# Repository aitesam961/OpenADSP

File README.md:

> An Embedded solution for Digital Signal Processing Applications in Audio signal processing.

## Table of contents
* [Description](https://github.com/maitesam/OpenADSP/blob/main/README.md#Description)
* [Block Diagram](https://github.com/maitesam/OpenADSP/blob/main/README.md#block-diagram)
* [Working Explained](https://github.com/maitesam/OpenADSP/blob/main/README.md#Working-Explained)
* [Ordering Boards](https://github.com/maitesam/OpenADSP/blob/main/README.md#Ordering-Boards)
* [Assembly](https://github.com/maitesam/OpenADSP/blob/main/README.md#Assembly)
* [Flashing Firmware](https://github.com/maitesam/OpenADSP/blob/main/README.md#Flashing-Firmware)
* [Contribution](https://github.com/maitesam/OpenADSP/blob/main/README.md#Contribution)
* [License](https://github.com/maitesam/OpenADSP/blob/main/README.md#License)

## Description
This device is designed to Take data from Microphone and Process it. Later it could be sent to a wirelessly connected devices Over Bluetooth.
Aside from this, the device can stream data to host computer over USB interface.

The PCB embedds a STM32L432 MCU which is extremely capable of handling Demanding tasks such as Digital Signal Processing.
The DSP scripts could be implemented in the firmware.

## Preview 

## Block Diagram
The Block Diagram Illustrates the connectivity inside The Board.

## Working Explained
This device is Designed for Digital Signal Processing applications.
The idea is to take Audio Data from a microphone, process it & Transmit to client devices.

#### What Type of Processing?
It features an STM32L432 Microcontroller with an ARM Cortex M4F (aka Black Pill). The device can be programmed to Apply Digital Filters and Effects on the audio data.
The very basic example is a Low Pass & High Pass filters.
The Incoming Audio Signal is converted to Digital (By ADC) and then Passed to STM32 which Applies programmed filters.

### Connectivity
The device is loaded with Two modes of communication.

* Bluetooth (2.4GHz)
* USB 2.0

The device is capable of Reading Data, applying filters and then Sending it wirelessly over to a Bluetooth Client
OR 
It Can be used as a USB OTG host device to send data stream over USB 2.0 Interface.

## Ordering Boards
You Can manufacture the PCBs from PCBWay.
[Check Out PCBWay](https://www.pcbway.com/setinvite.aspx?inviteid=440401)

Note: I am not affiliated with PCBWay. However, I just like their service and build quality.

## Assembly Guide
Please Refer to [Hardware Readme](https://github.com/maitesam/OpenADSP/blob/main/Hardware) for Assembly Instructions.

## Flashing Firmware
Please Refer to [Firmware Readme](https://github.com/maitesam/OpenADSP/tree/main/Firmware) to find more details about Flashing FIrmware.

### Contributions

Contributions are what make the open source community such an amazing place to learn, inspire, and create. Any contributions you make are **greatly appreciated**.

If you have a suggestion that would make this better, please fork the repo and create a pull request. You can also simply open an issue with the tag "enhancement".
Don't forget to give the project a star! Thanks again!

1. Fork the Project
2. Create your Feature Branch (`git checkout -b feature/AmazingFeature`)
3. Commit your Changes (`git commit -m 'Add some AmazingFeature'`)
4. Push to the Branch (`git push origin feature/AmazingFeature`)
5. Open a Pull Request

## Roadmap

* [x] Concept Proof
* [x] Research & Information
* [x] Finalizing The Idea
* [x] Schematics
* [x] PCB Design
* [ ] Firmware Development
* [ ] Validation & Testing
* [ ] Documentation
* [ ] Future Improvements

## File Tree

```
.
├── Datasheets
│   ├── AP2112-3.3V.pdf
│   ├── nRF24L01.pdf
│   ├── Readme.md
│   ├── SRV05-4-D.PDF
│   ├── stm32l432kb.pdf
│   └── tlv320aic3100 codec.pdf
├── Documents
│   ├── Code_Print.pdf
│   ├── ibom.html
│   ├── OpenADSP_BLD.jpg
│   ├── OpenADSP_BLD.png
│   ├── PCB Layers
│   │   ├── Audio_Processing_HW_V1.0-B_Adhesive.svg
│   │   ├── Audio_Processing_HW_V1.0-B_Cu.svg
│   │   ├── Audio_Processing_HW_V1.0-B_Mask.svg
│   │   ├── Audio_Processing_HW_V1.0-B_Paste.svg
│   │   ├── Audio_Processing_HW_V1.0-B_Silkscreen.svg
│   │   ├── Audio_Processing_HW_V1.0-Edge_Cuts.svg
│   │   ├── Audio_Processing_HW_V1.0-F_Adhesive.svg
│   │   ├── Audio_Processing_HW_V1.0-F_Cu.svg
│   │   ├── Audio_Processing_HW_V1.0-F_Mask.svg
│   │   ├── Audio_Processing_HW_V1.0-F_Paste.svg
│   │   └── Audio_Processing_HW_V1.0-F_Silkscreen.svg
│   ├── PCB_LayerWise_Export.pdf
│   └── Schematic_OpenADSP.pdf
├── Firmware
│   ├── OpenADSP Debug.launch
│   ├── OpenADSP.ioc
│   ├── Readme.md
│   ├── STM32L432KBUX_FLASH.ld
│   └── temp.html
├── Hardware
│   ├── Analog Filters.kicad_sch
│   ├── Audio_Processing_HW_V1.0.kicad_pcb
│   ├── Audio_Processing_HW_V1.0.kicad_pro
│   ├── Audio_Processing_HW_V1.0.kicad_sch
│   ├── MCU.kicad_sch
│   ├── Power & USB.kicad_sch
│   ├── Readme.md
│   ├── STM32 MCU.kicad_sch
│   ├── untitled.kicad_sch
│   ├── USB&POWER.kicad_sch
│   └── Wireless Tranceiver.kicad_sch
├── Images
│   ├── Bottom_Flat.png
│   ├── Side_Front_view.jpg
│   └── Top_Flat.png
├── LICENSE
├── Mechanical_Files
│   ├── Audio_Processing_HW_V1.0.step
│   ├── Audio_Processing_HW_V1.0.wrl
│   └── readme.txt
├── Readme Docs
│   ├── banner.png
│   ├── ezgif.com-gif-maker.gif
│   ├── icon-5974829_1280.png
│   ├── OpenADSP BOM and 6 more pages - Personal - Microsoft​ Edge 2022-03-02 17-06-42_Trim.mp4
│   ├── OpenADSP.jpg
│   ├── OpenADSP.png
│   └── sound-1837425_1280.png
├── README.md
└── Reference Files
    ├── an4157-stm32f3discovery-peripheral-firmware-examples-stmicroelectronics.pdf
    ├── Deleteme.html
    ├── en.MB1035-F303C-C01_Schematic.pdf
    ├── en.MB1035-F303C-D01_Schematic.pdf
    └── en.MB1035-F303C-E02_Schematic.pdf

9 directories, 59 files

```
## License

This Project is published under General Public License V3.0 See `LICENSE.txt` for more information.
> https://www.gnu.org/licenses/quick-guide-gplv3.html

<p align="right">(<a href="#top">back to top</a>)</p>

* [Jump To Start](https://github.com/maitesam/OpenADSP/blob/main/README.md#Description)

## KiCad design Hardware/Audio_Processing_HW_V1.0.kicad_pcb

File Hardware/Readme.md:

# Readme
## Getting started with Hardware
### Assembly Instructions
Before you start, Get the proper set of equipment.

* The Third Hand is always helpful in assembly. I recommend using some soldering Jig or Stickvise Jaws 
* Its super handy to have a cutting knife
* Better have some Non Serrated Pliers
* Obviously, A soldering Iron
* Solder Paste would be useful
* Great to have some extra Soldering Iron tips to get the perfect size

The Soldering Kit below May give you a good idea of what you need.

## General tips

 * Keep both the schematics and the board file open while you build, you'll likely want to refer back to them more often than not.
 Even I got you covered here. This [Interactive BOM](https://github.com/maitesam/OpenADSP/blob/main/Documents/ibom.html) will help you out locating the components and their references.
 Just Download the file and Open it in your Browser.
 It should present you with something like this

 * I wholeheartedly recommend this thread by [@thingskatedid](https://twitter.com/thingskatedid): https://twitter.com/thingskatedid/status/1348234262886039558

 * **The passives are indistinguishable once taken out of their tapes!**
   * Always work with a single value at a time
   * Only remove as many components from the tape as you need right now
   * Immediately put the tape back into the pouch it came in, as that's where the value is noted - or write the value onto the tape.

 * For each group of passives below, it saves time to batch up different types of operations: First put a small solder blob on one pad of each site, then tack down each component, then solder the other side for all components in a row.

 * If the solder joints on nearby passives blob together a lot, use some flux and a little less solder. It's also a good idea to make a final flux pass across the finished passives just like you would be drag soldering a leaded part, it makes the solder joints look a lot nicer.

### Assembly instructions

These instructions are optimized for hand assembly; the components are grouped in a way that if you follow the groups in order you should never have one component in the way of soldering another. Within a given group the order does not matter; I recommend doing all components of one value before moving on to the next value.

I found this Tutorial Video by @Electronoobs really helpful.

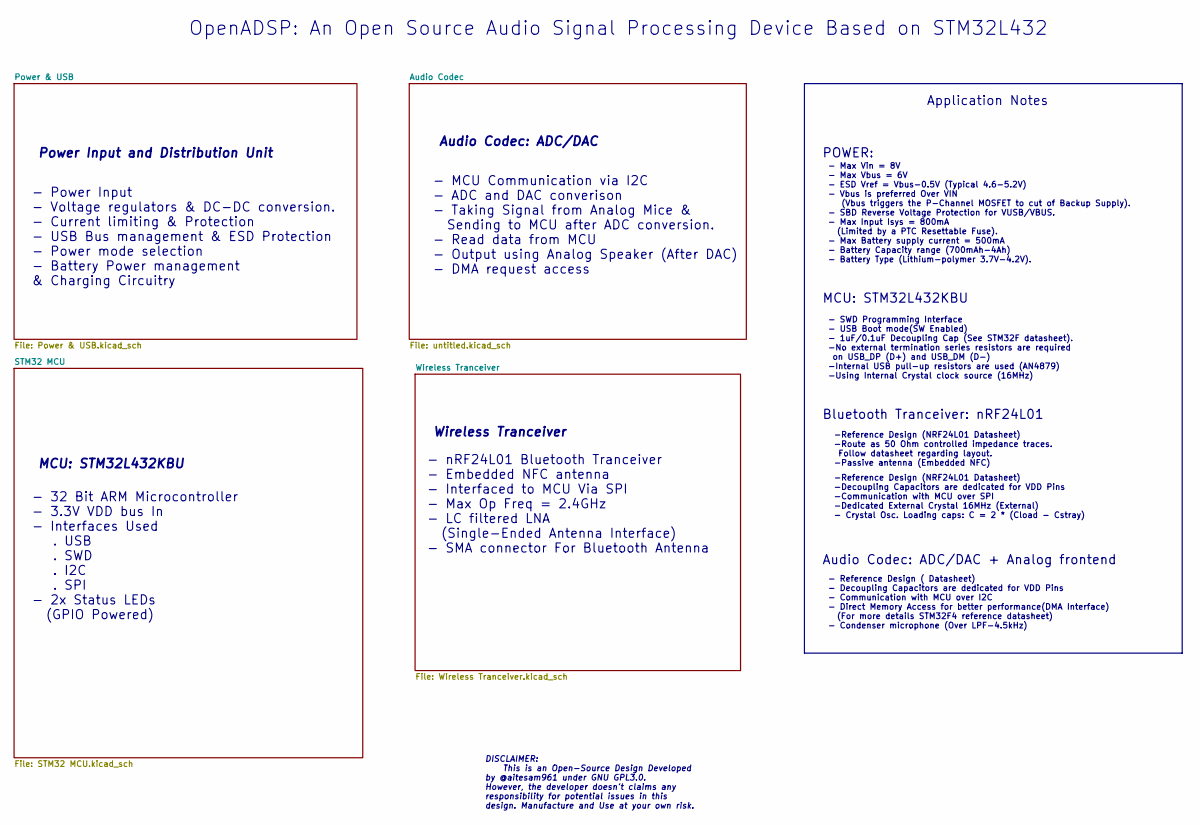
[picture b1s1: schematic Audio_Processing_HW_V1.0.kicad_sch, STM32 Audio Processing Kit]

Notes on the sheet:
OpenADSP: An Open Source Audio Signal Processing Device Based on STM32L432
Audio Codec: ADC/DAC
MCU: STM32L432KBU
- MCU Communication via I2C - ADC and DAC converison - Taking Signal from Analog Mice & Sending to MCU after ADC conversion. - Read data from MCU - Output using Analog Speaker (After DAC) - DMA request access
- nRF24L01 Bluetooth Tranceiver - Embedded NFC antenna - Interfaced to MCU Via SPI - Max Op Freq = 2.4GHz - LC filtered LNA (Single-Ended Antenna Interface) - SMA connector For Bluetooth Antenna
MCU: STM32L432KBU
POWER:
- Reference Design ( Datasheet) - Decoupling Capacitors are dedicated for VDD Pins - Communication with MCU over I2C - Direct Memory Access for better performance(DMA Interface) (For more details STM32F4 reference datasheet) - Condenser microphone (Over LPF-4.5kHz)
- Power Input - Voltage regulators & DC-DC conversion. - Current limiting & Protection - USB Bus management & ESD Protection - Power mode selection - Battery Power management & Charging Circuitry
-Reference Design (NRF24L01 Datasheet) -Decoupling Capacitors are dedicated for VDD Pins -Communication with MCU over SPI -Dedicated External Crystal 16MHz (External) - Crystal Osc. Loading caps: C = 2 * (Cload - Cstray)
Power Input and Distribution Unit
- 32 Bit ARM Microcontroller - 3.3V VDD bus In - Interfaces Used . USB . SWD . I2C . SPI - 2x Status LEDs (GPIO Powered)
Application Notes
- Max Vin = 8V - Max Vbus = 6V - ESD Vref = Vbus-0.5V (Typical 4.6-5.2V) - Vbus is preferred Over VIN (Vbus triggers the P-Channel MOSFET to cut of Backup Supply). - SBD Reverse Voltage Protection for VUSB/VBUS. - Max Input Isys = 800mA (Limited by a PTC Resettable Fuse). - Max Battery supply curre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
Audio Codec: ADC/DAC + Analog frontend
-Reference Design (NRF24L01 Datasheet) -Route as 50 Ohm controlled impedance traces. Follow datasheet regarding layout. -Passive antenna (Embedded NFC)
Bluetooth Tranceiver: nRF24L01
- SWD Programming Interface - USB Boot mode(SW Enabled) - 1uF/0.1uF Decoupling Cap (See STM32F datasheet). -No external termination series resistors are required on USB_DP (D+) and USB_DM (D-) -Internal USB pull-up resistors are used (AN4879) -Using Internal Crystal clock source (16MHz)
Wireless Tranceiver
DISCLAIMER: This is an Open-Source Design Developed by @aitesam961 under GNU GPL3.0. However, the developer doesn't claims any responsibility for potential issues in this design. Manufacture and Use at your own risk.

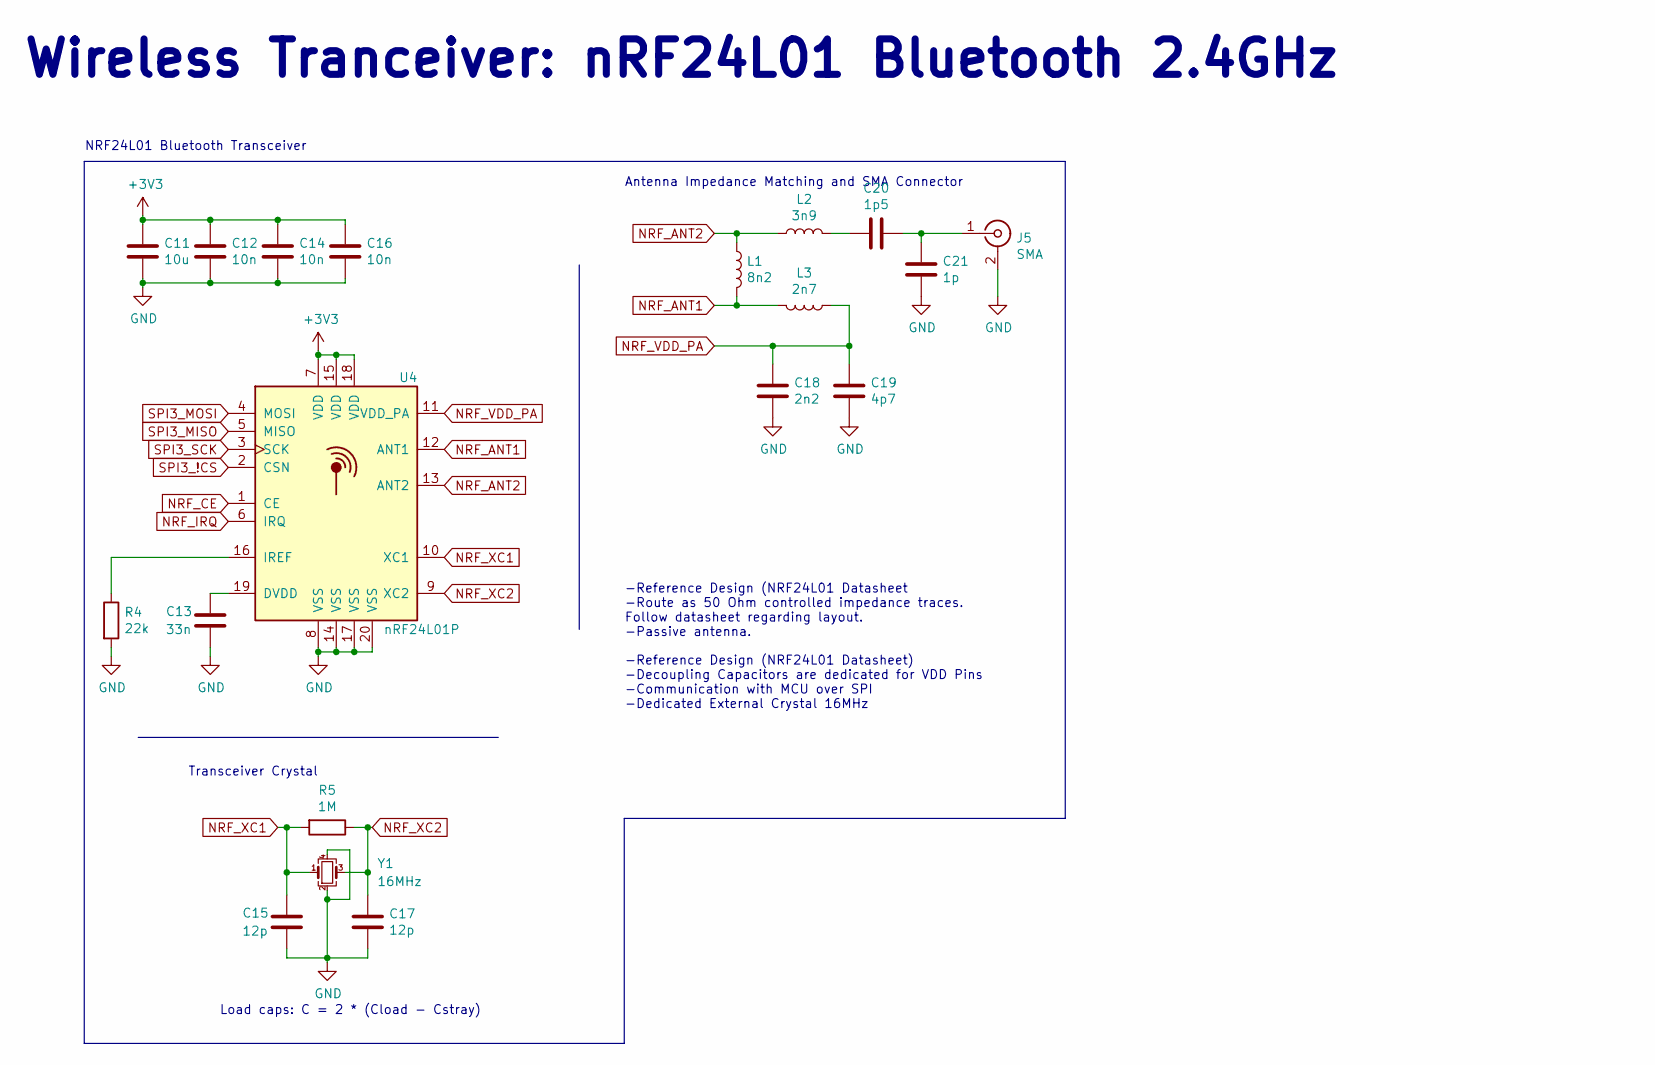
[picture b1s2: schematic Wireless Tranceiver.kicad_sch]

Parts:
C11: 10u; C_0603_1608Metric
C12, C14, C16: 10n; C_0402_1005Metric
C13: 33n; C_0402_1005Metric
C15, C17: 12p; C_0402_1005Metric
C18: 2n2; C_0402_1005Metric
C19: 4p7; C_0402_1005Metric
C20: 1p5; C_0402_1005Metric
C21: 1p; C_0402_1005Metric
J5: SMA; SMA_Samtec_SMA-J-P-X-ST-EM1_EdgeMount
L1: 8n2; L_0402_1005Metric
L2: 3n9; L_0402_1005Metric
L3: 2n7; L_0402_1005Metric
R4: 22k; R_0402_1005Metric
R5: 1M; R_0402_1005Metric
U4: nRF24L01P; QFN-20-1EP_4x4mm_P0.5mm_EP2.5x2.5mm
Y1: 16MHz; Crystal_SMD_3225-4Pin_3.2x2.5mm

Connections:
+3V3: C11.1, C12.1, C14.1, C16.1, U4.7 (VDD), U4.15 (VDD), U4.18 (VDD); also elsewhere on the board
GND: C11.2, C12.2, C13.2, C14.2, C15.2, C16.2, C17.2, C18.1, C19.1, C21.1, J5.2 (Ext), R4.2, U4.8 (VSS), U4.14 (VSS), U4.17 (VSS), U4.20 (VSS), Y1.2, Y1.4; also elsewhere on the board
NRF_ANT1: L1.2, L3.2, U4.12 (ANT1)
NRF_ANT2: L1.1, L2.1, U4.13 (ANT2)
NRF_CE: U4.1 (CE); also elsewhere on the board
NRF_IRQ: U4.6 (IRQ); also elsewhere on the board
NRF_VDD_PA: C18.2, C19.2, L3.1, U4.11 (VDD_PA)
NRF_XC1: C15.1, R5.2, U4.10 (XC1), Y1.1
NRF_XC2: C17.1, R5.1, U4.9 (XC2), Y1.3
unnamed: C13.1, U4.19 (DVDD)
unnamed: C20.1, C21.2, J5.1 (In)
unnamed: C20.2, L2.2
unnamed: R4.1, U4.16 (IREF)
SPI3_!CS: U4.2 (CSN); also elsewhere on the board
SPI3_MISO: U4.5 (MISO); also elsewhere on the board
SPI3_MOSI: U4.4 (MOSI); also elsewhere on the board
SPI3_SCK: U4.3 (SCK); also elsewhere on the board

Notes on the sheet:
NRF24L01 Bluetooth Transceiver
-Reference Design (NRF24L01 Datasheet) -Decoupling Capacitors are dedicated for VDD Pins -Communication with MCU over SPI -Dedicated External Crystal 16MHz
Transceiver Crystal
Antenna Impedance Matching and SMA Connector
Load caps: C = 2 * (Cload - Cstray)
-Reference Design (NRF24L01 Datasheet -Route as 50 Ohm controlled impedance traces. Follow datasheet regarding layout. -Passive antenna.
Wireless Tranceiver: nRF24L01 Bluetooth 2.4GHz

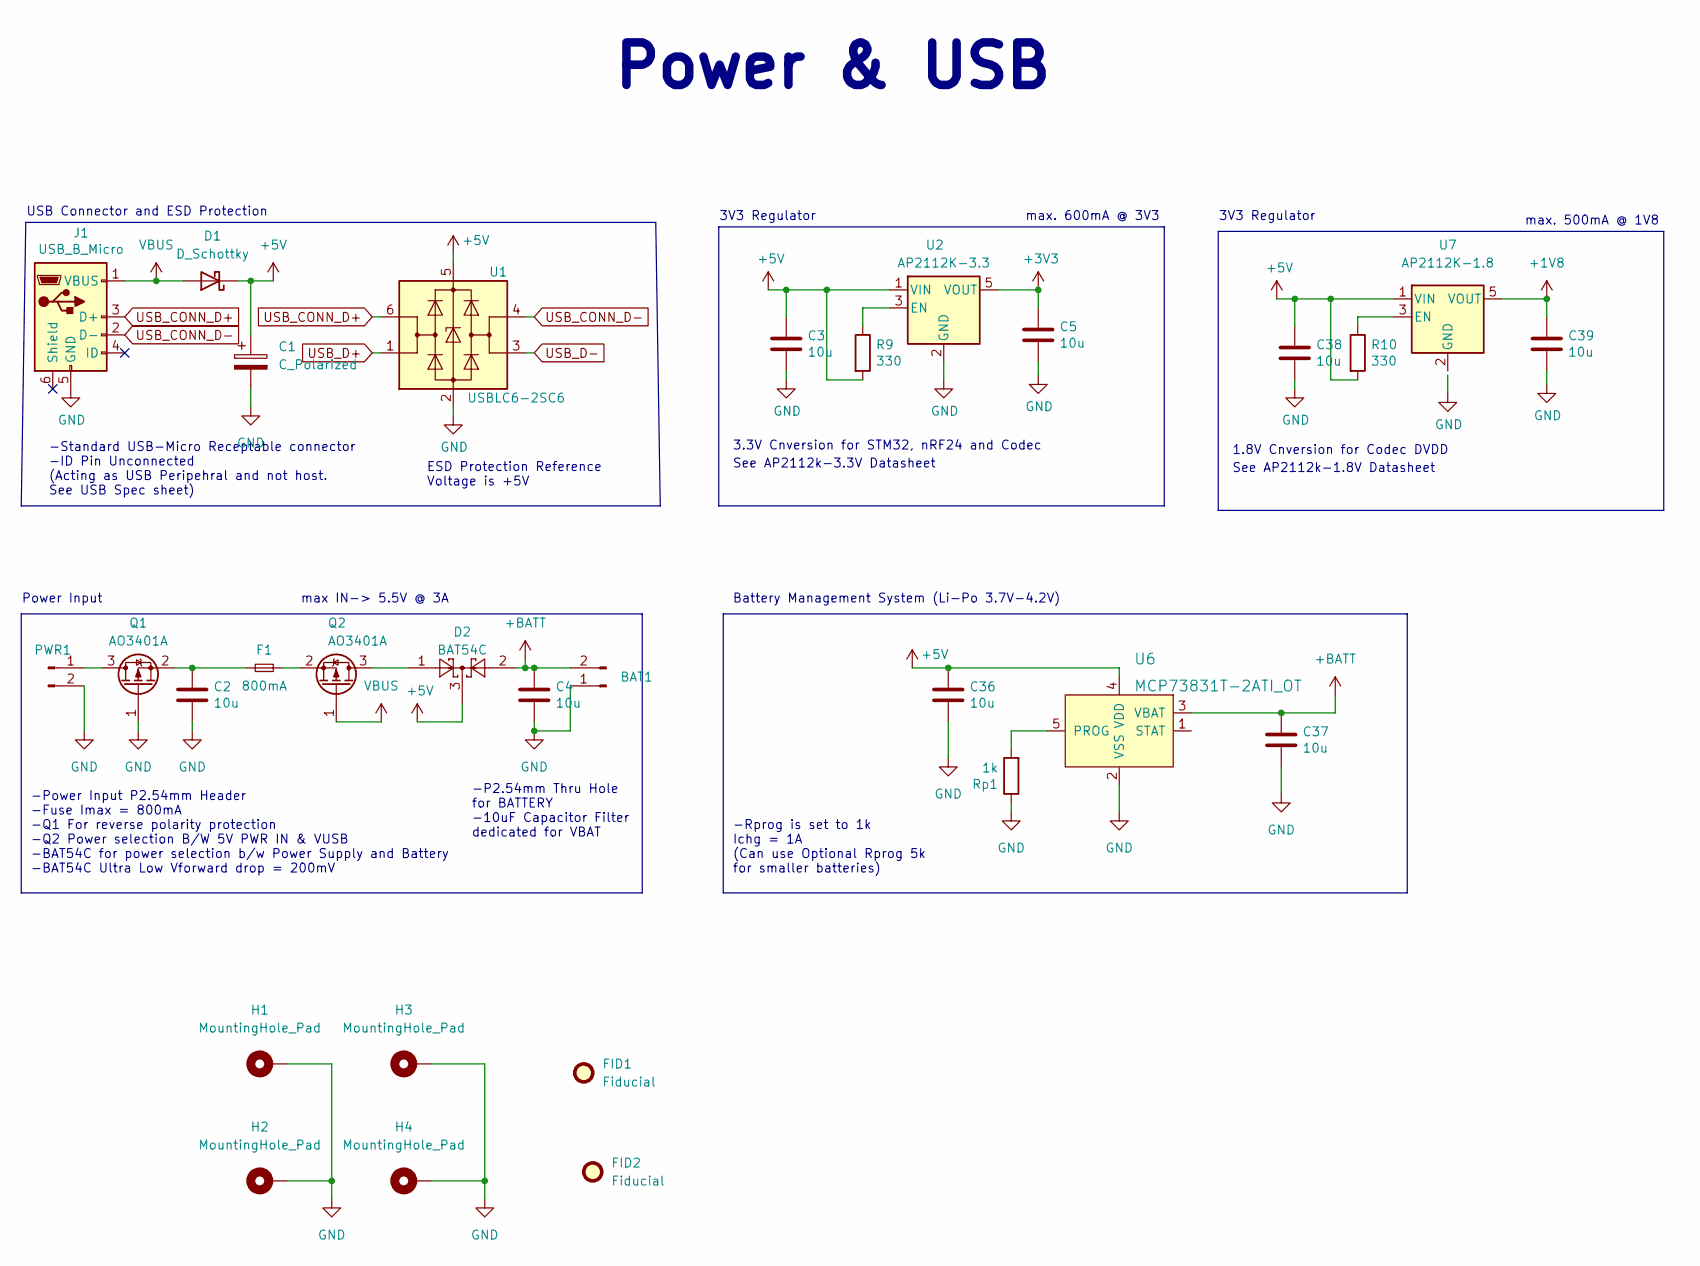
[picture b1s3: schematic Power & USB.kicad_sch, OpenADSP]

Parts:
BAT1: Conn_01x02_Male; PinHeader_1x02_P2.54mm_Vertical
C1: C_Polarized; CP_EIA-3528-12_Kemet-T
C2, C3, C4, C5, C36, C37, C38, C39: 10u; C_0603_1608Metric
D1: D_Schottky; D_0603_1608Metric
D2: BAT54C; SOT-23
F1: 800mA; Fuse_0603_1608Metric
FID1, FID2: Fiducial; Fiducial_0.75mm_Mask1.5mm
H1, H2, H3, H4: MountingHole_Pad; MountingHole_2.5mm_Pad_Via
J1: USB_B_Micro; USB_Micro-B_Wuerth_629105150521
PWR1: Conn_01x02_Male; PinHeader_1x02_P2.54mm_Vertical
Q1, Q2: AO3401A; SOT-23
R9, R10: 330; R_0402_1005Metric
Rp1: 1k; R_0402_1005Metric
U1: USBLC6-2SC6; SOT-23-6
U2: AP2112K-3.3; SOT-23-5
U6: MCP73831T-2ATI_OT; SOT-753; MPN MCP73831T-2ATI/OT; Digi-Key_PN MCP73831T-2ATI/OTCT-ND
U7: AP2112K-1.8; SOT-23-5

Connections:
+1V8: C39.1, U7.5 (VOUT); also elsewhere on the board
+3V3: C5.1, U2.5 (VOUT); also elsewhere on the board
+5V: C1.1, C3.1, C36.1, C38.1, D1.1 (K), D2.3, R9.2, R10.2, U1.5 (VBUS), U2.1 (VIN), U6.4 (VDD), U7.1 (VIN); also elsewhere on the board
+BATT: BAT1.2, C4.1, C37.1, D2.2, U6.3 (VBAT)
GND: BAT1.1, C1.2, C2.2, C3.2, C4.2, C5.2, C36.2, C37.2, C38.2, C39.2, H1.1, H2.1, H3.1, H4.1, J1.5 (GND), PWR1.2, Q1.1 (G), Rp1.1, U1.2 (GND), U2.2 (GND), U6.2 (VSS); also elsewhere on the board
unnamed: C2.1, F1.1, Q1.2 (S)
unnamed: D2.1, Q2.3 (D)
unnamed: F1.2, Q2.2 (S)
unnamed: PWR1.1, Q1.3 (D)
unnamed: R10.1, U7.3 (EN)
unnamed: Rp1.2, U6.5 (PROG)
unnamed: R9.1, U2.3 (EN)
USB_CONN_D+: J1.3 (D+), U1.6 (I/O1)
USB_CONN_D-: J1.2 (D-), U1.4 (I/O2)
USB_D+: U1.1 (I/O1); also elsewhere on the board
USB_D-: U1.3 (I/O2); also elsewhere on the board
VBUS: D1.2 (A), J1.1 (VBUS), Q2.1 (G)

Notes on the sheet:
1.8V Cnversion for Codec DVDD
-Rprog is set to 1k Ichg = 1A (Can use Optional Rprog 5k for smaller batteries)
-P2.54mm Thru Hole for BATTERY -10uF Capacitor Filter dedicated for VBAT
-Standard USB-Micro Receptable connector -ID Pin Unconnected (Acting as USB Peripehral and not host. See USB Spec sheet)
Power & USB
3V3 Regulator
max. 500mA @ 1V8
Battery Management System (Li-Po 3.7V-4.2V)
max. 600mA @ 3V3
ESD Protection Reference Voltage is +5V
See AP2112k-1.8V Datasheet
3.3V Cnversion for STM32, nRF24 and Codec
USB Connector and ESD Protection
Power Input
See AP2112k-3.3V Datasheet
-Power Input P2.54mm Header -Fuse Imax = 800mA -Q1 For reverse polarity protection -Q2 Power selection B/W 5V PWR IN & VUSB -BAT54C for power selection b/w Power Supply and Battery -BAT54C Ultra Low Vforward drop = 200mV
max IN-> 5.5V @ 3A

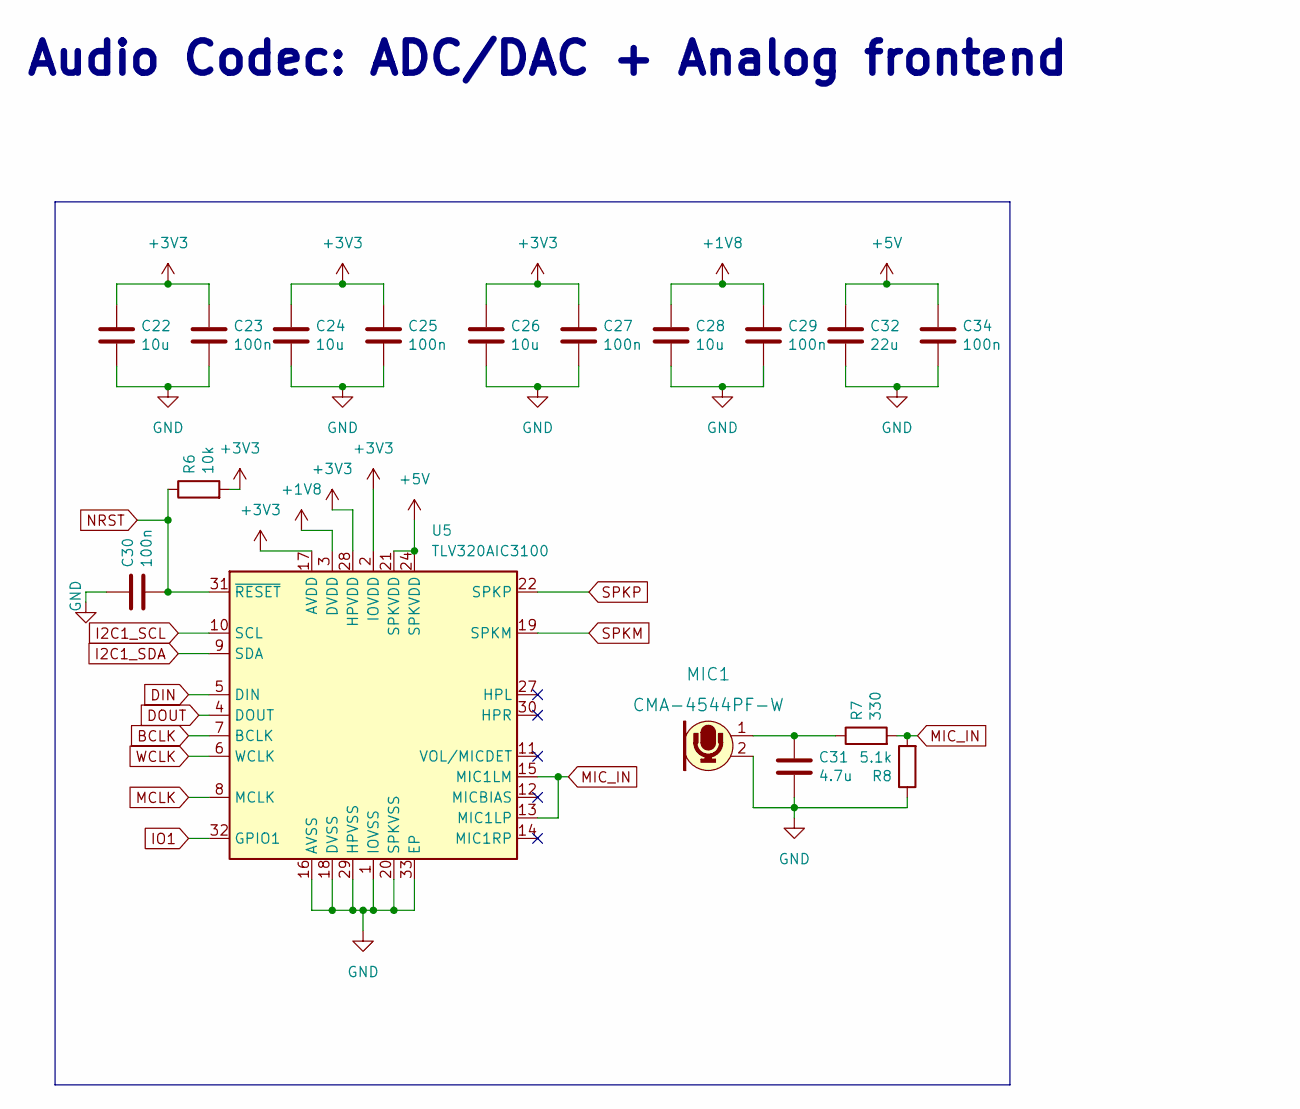
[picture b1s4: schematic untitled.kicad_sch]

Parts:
C22, C24, C26, C28: 10u; C_0402_1005Metric
C23, C25, C27, C29, C30, C34: 100n; C_0402_1005Metric
C31: 4.7u; C_0402_1005Metric
C32: 22u; C_0402_1005Metric
MIC1: CMA-4544PF-W; Mic_CMA-4544PF-W; MPN CMA-4544PF-W; Digi-Key_PN 102-1721-ND
R6: 10k; R_0402_1005Metric
R7: 330; R_0402_1005Metric
R8: 5.1k; R_0402_1005Metric
U5: TLV320AIC3100; VQFN-32-1EP_5x5mm_P0.5mm_EP3.5x3.5mm

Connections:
+1V8: C28.1, C29.1, U5.3 (DVDD); also elsewhere on the board
+3V3: C22.1, C23.1, C24.1, C25.1, C26.1, C27.1, R6.2, U5.2 (IOVDD), U5.17 (AVDD), U5.28 (HPVDD); also elsewhere on the board
+5V: C32.1, C34.1, U5.21 (SPKVDD), U5.24 (SPKVDD); also elsewhere on the board
BCLK: U5.7 (BCLK); also elsewhere on the board
DIN: U5.5 (DIN); also elsewhere on the board
DOUT: U5.4 (DOUT); also elsewhere on the board
GND: C22.2, C23.2, C24.2, C25.2, C26.2, C27.2, C28.2, C29.2, C30.1, C31.2, C32.2, C34.2, MIC1.2, R8.1, U5.1 (IOVSS), U5.16 (AVSS), U5.18 (DVSS), U5.20 (SPKVSS), U5.25 (SPKVSS), U5.29 (HPVSS), U5.33 (EP); also elsewhere on the board
I2C1_SCL: U5.10 (SCL); also elsewhere on the board
I2C1_SDA: U5.9 (SDA); also elsewhere on the board
IO1: U5.32 (GPIO1); also elsewhere on the board
MCLK: U5.8 (MCLK); also elsewhere on the board
MIC_IN: R7.2, R8.2, U5.13 (MIC1LP), U5.15 (MIC1LM)
NRST: C30.2, R6.1, U5.31 (~RESET); also elsewhere on the board
unnamed: C31.1, MIC1.1, R7.1
SPKM: U5.19 (SPKM), U5.23 (SPKM)
SPKP: U5.22 (SPKP), U5.26 (SPKP)
WCLK: U5.6 (WCLK); also elsewhere on the board

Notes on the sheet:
Audio Codec: ADC/DAC + Analog frontend

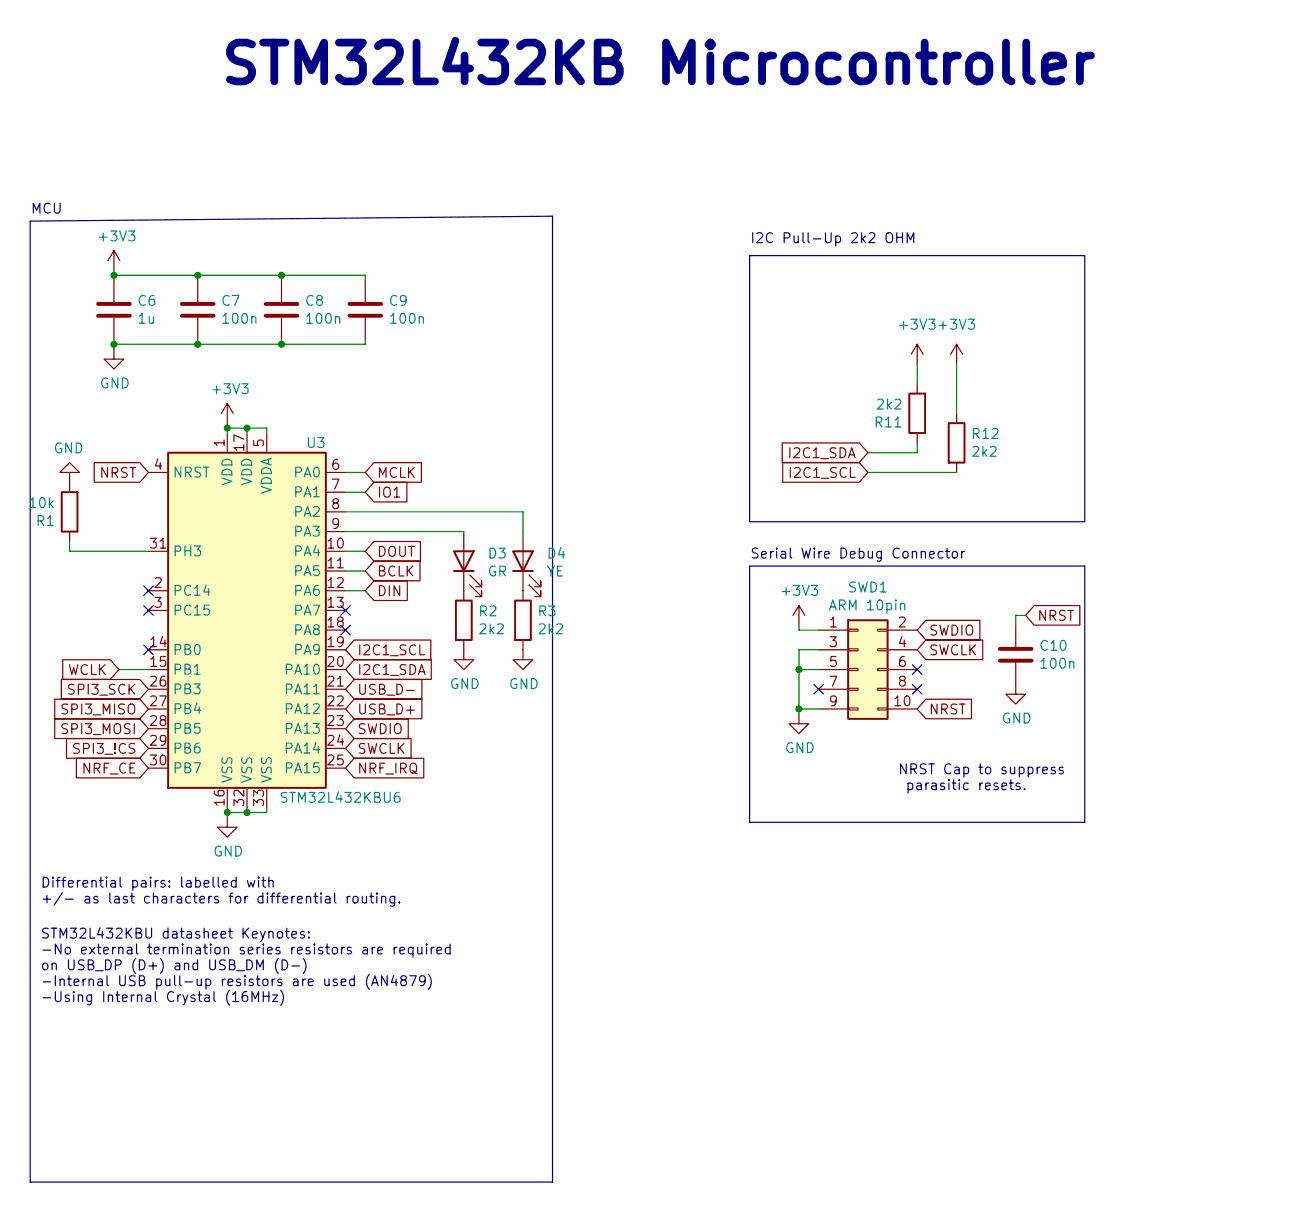
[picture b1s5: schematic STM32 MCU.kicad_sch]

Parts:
C6: 1u; C_0402_1005Metric
C7, C8, C9, C10: 100n; C_0402_1005Metric
D3: GR; LED_0603_1608Metric
D4: YE; LED_0603_1608Metric
R1: 10k; R_0402_1005Metric
R2, R3: 2k2; R_0603_1608Metric
R11, R12: 2k2; R_0402_1005Metric
SWD1: ARM 10pin; PinHeader_2x05_P1.27mm_Vertical
U3: STM32L432KBU6; QFN-32-1EP_5x5mm_P0.5mm_EP3.45x3.45mm

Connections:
+3V3: C6.1, C7.1, C8.1, C9.1, R11.2, R12.1, SWD1.1, U3.1 (VDD), U3.5 (VDDA), U3.17 (VDD); also elsewhere on the board
BCLK: U3.11 (PA5); also elsewhere on the board
DIN: U3.12 (PA6); also elsewhere on the board
DOUT: U3.10 (PA4); also elsewhere on the board
GND: C6.2, C7.2, C8.2, C9.2, C10.2, R1.2, R2.2, R3.2, SWD1.3, SWD1.5, SWD1.9, U3.16 (VSS), U3.32 (VSS), U3.33 (VSS); also elsewhere on the board
I2C1_SCL: R12.2, U3.19 (PA9); also elsewhere on the board
I2C1_SDA: R11.1, U3.20 (PA10); also elsewhere on the board
IO1: U3.7 (PA1); also elsewhere on the board
MCLK: U3.6 (PA0); also elsewhere on the board
NRF_CE: U3.30 (PB7); also elsewhere on the board
NRF_IRQ: U3.25 (PA15); also elsewhere on the board
NRST: C10.1, SWD1.10, U3.4 (NRST); also elsewhere on the board
unnamed: D3.1 (K), R2.1
unnamed: D3.2 (A), U3.9 (PA3)
unnamed: D4.1 (K), R3.1
unnamed: D4.2 (A), U3.8 (PA2)
unnamed: R1.1, U3.31 (PH3)
SPI3_!CS: U3.29 (PB6); also elsewhere on the board
SPI3_MISO: U3.27 (PB4); also elsewhere on the board
SPI3_MOSI: U3.28 (PB5); also elsewhere on the board
SPI3_SCK: U3.26 (PB3); also elsewhere on the board
SWCLK: SWD1.4, U3.24 (PA14)
SWDIO: SWD1.2, U3.23 (PA13)
USB_D+: U3.22 (PA12); also elsewhere on the board
USB_D-: U3.21 (PA11); also elsewhere on the board
WCLK: U3.15 (PB1); also elsewhere on the board

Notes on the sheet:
STM32L432KBU datasheet Keynotes: -No external termination series resistors are required on USB_DP (D+) and USB_DM (D-) -Internal USB pull-up resistors are used (AN4879) -Using Internal Crystal (16MHz)
Serial Wire Debug Connector
NRST Cap to suppress parasitic resets.
Differential pairs: labelled with +/- as last characters for differential routing.
STM32L432KB Microcontroller
MCU
I2C Pull-Up 2k2 OHM

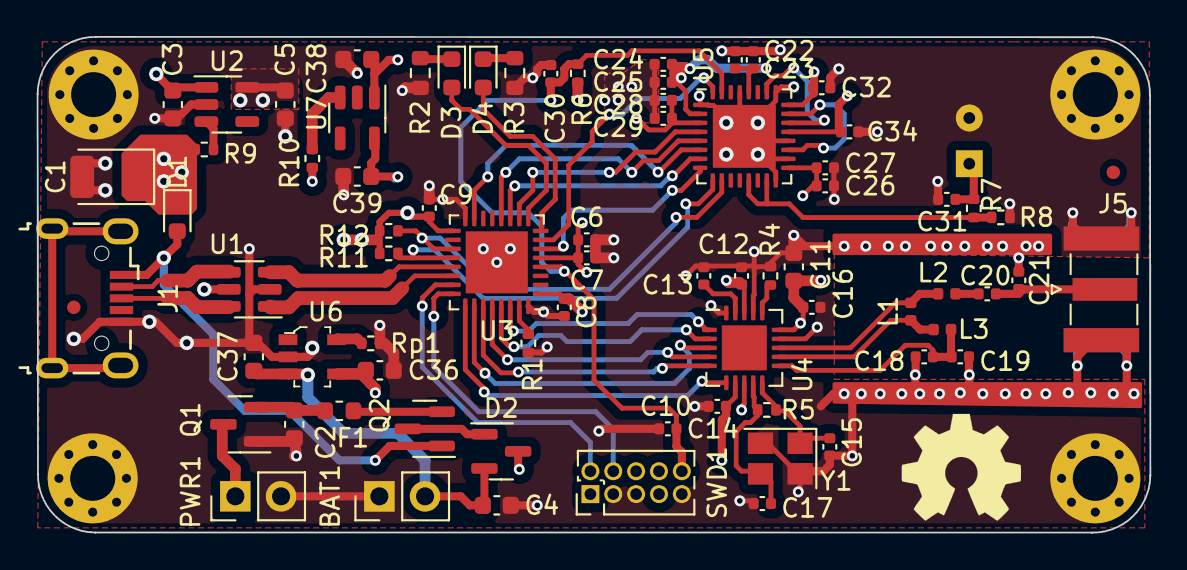
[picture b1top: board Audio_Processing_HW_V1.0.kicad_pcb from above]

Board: 4 copper layers, 61.8 x 27.5 mm, 80 parts (1 on the bottom side), 52 nets.

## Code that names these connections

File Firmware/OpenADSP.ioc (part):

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Mcu.Name=STM32L432K(B-C)Ux
Mcu.Package=UFQFPN32
Mcu.UserName=STM32L432KBUx
PA0.Mode=HSE-External-Clock-Source-for-LittleOrca
PA0.Signal=RCC_CK_IN
PA1.Mode=Full_Duplex_Master
PA1.Signal=SPI1_SCK
PA10.Mode=SMBus-two-wire-Interface
PA10.Signal=I2C1_SDA
PA11.Mode=Device
PA11.Signal=USB_DM
PA12.Mode=Device
PA12.Signal=USB_DP
PA13\ (JTMS-SWDIO).Mode=Trace_Asynchronous_SW
PA13\ (JTMS-SWDIO).Signal=SYS_JTMS-SWDIO
PA14\ (JTCK-SWCLK).Mode=Trace_Asynchronous_SW
PA14\ (JTCK-SWCLK).Signal=SYS_JTCK-SWCLK
PA15\ (JTDI).Signal=GPIO_Output
PA2.Signal=S_TIM2_CH3
PA4.Signal=GPIO_Output
PA5.Signal=GPIO_Output
PA6.Signal=GPIO_Input
PA9.Mode=SMBus-two-wire-Interface
PA9.Signal=I2C1_SCL
PB1.Signal=GPIO_Output
PB3\ (JTDO-TRACESWO).Mode=Trace_Asynchronous_SW
PB3\ (JTDO-TRACESWO).Signal=SYS_JTDO-SWO
PB4\ (NJTRST).Mode=Full_Duplex_Master
PB4\ (NJTRST).Signal=SPI1_MISO
PB5.Mode=Full_Duplex_Master
PB5.Signal=SPI1_MOSI
PB6.Signal=GPIO_Output
PB7.Signal=GPIO_Output
PC14-OSC32_IN\ (PC14).Mode=LSE-External-Oscillator
PC14-OSC32_IN\ (PC14).Signal=RCC_OSC32_IN
PC15-OSC32_OUT\ (PC15).Mode=LSE-External-Oscillator
PC15-OSC32_OUT\ (PC15).Signal=RCC_OSC32_OUT
PH3-BOOT0.Signal=GPIO_Output
RCC.HSE_VALUE=16000000
RCC.SYSCLKFreq_VALUE=16000000
RCC.SYSCLKSource=RCC_SYSCLKSOURCE_HSE
board=custom

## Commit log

2022-02-28 Create Hardware
2022-02-28 Created Hardware Folder
2022-02-28 Uploaded KiCad Project Source Files
    A Complete set of source files
    KiCad V6.0
2022-02-28 Created new Folder, Documents
2022-02-28 Uploaded STM32CubeIDE Project Source Files
2022-03-01 Uploaded Banner
2022-03-01 OpenADSP
    OpenADSP is a Digital Signal Processing device designed to process and transmit Audio signals over wired & wireless communication protocols
2022-03-01 Readme Updated
2022-03-01 Updated Readme & Documentation

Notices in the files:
Hardware/Audio_Processing_HW_V1.0.kicad_pcb:
This is an Open-Source Design Developed using the best practices and
documentation available. It is available under GNU General Public License 3.0 .
